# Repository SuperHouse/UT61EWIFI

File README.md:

UNI-T UT61E Multimeter WiFi Interface
=====================================

The UNI-T UT61E multimeter has an opto-isolated output port that
streams data, including the currently selected range and reading.

This project is a WiFi adapter that attaches to the output port
and reports the data via WiFi or USB.

The example firmware reads the data packet from the multimeter and
publishes it to an MQTT broker, and also outputs it via the USB
port at 115200bps.

NOTE: The Rx data pin has been changed from D0 (GPIO16) in the
v1.0 design to D5 (GPIO14) in v1.1. Photos show a v1.0 PCB that
has been patched to the new Rx data pin.

More details:

  http://www.superhouse.tv/ut61ewifi

Releases
--------
See latest release here: (https://github.com/SuperHouse/UT61EWIFI/releases)[https://github.com/SuperHouse/UT61EWIFI/releases]  

Clients
--------
To build the app locally, you can run ```bash ./Clients/build/build.sh``` from the ```/``` (root) of this repo.  
It will run a build of all the clients. (*nodeJS v16 and bash are required*)

Hardware
--------
The "Hardware" directory contains the PCB design as an EAGLE project.
EAGLE PCB design software is available from Autodesk free for
non-commercial use.

Firmware
--------
The "Firmware" directory contains example firmware as an Arduino
project.

The Wemos D1 Mini used in the adapter has an Espressif ESP8266 MCU. 
This is not supported by default by the Arduino IDE, so the first 
step is to install a board profile to suit.

Full steps are explained here:

<https://randomnerdtutorials.com/how-to-install-esp8266-board-arduino-ide/>

Then select: 

  Tools -> Board -> ESP8266 Boards -> "WEMOS(LOLIN) D1 Mini (clone)".

Other ESP8266 board profiles may also work, depending on the specific 
D1 mini that you use.

Two libraries are also required. Install using the Arduino library manager: 

 * "PubSubClient" by Nick O'Leary
 * "NeoPixel" by Adafruit

Credits
-------
  * Jonathan Oxer <jon@oxer.com.au>
  * CableTie <https://github.com/cabletie>
  * Aaron Knox <aaron@makerdock.io>
  * Mitchell Robert <https://github.com/mrinc>

License
-------
Copyright 2021 SuperHouse Automation Pty Ltd  www.superhouse.tv  

The hardware portion of this project is licensed under the TAPR Open
Hardware License (www.tapr.org/OHL). The "license" folder within this
repository contains a copy of this license in plain text format.

The software portion of this project is licensed under the Simplified
BSD License. The "licence" folder within this project contains a
copy of this license in plain text format.

The UNI-T logo is the trademark of Uni-Trend Technology (China) Co., Ltd.

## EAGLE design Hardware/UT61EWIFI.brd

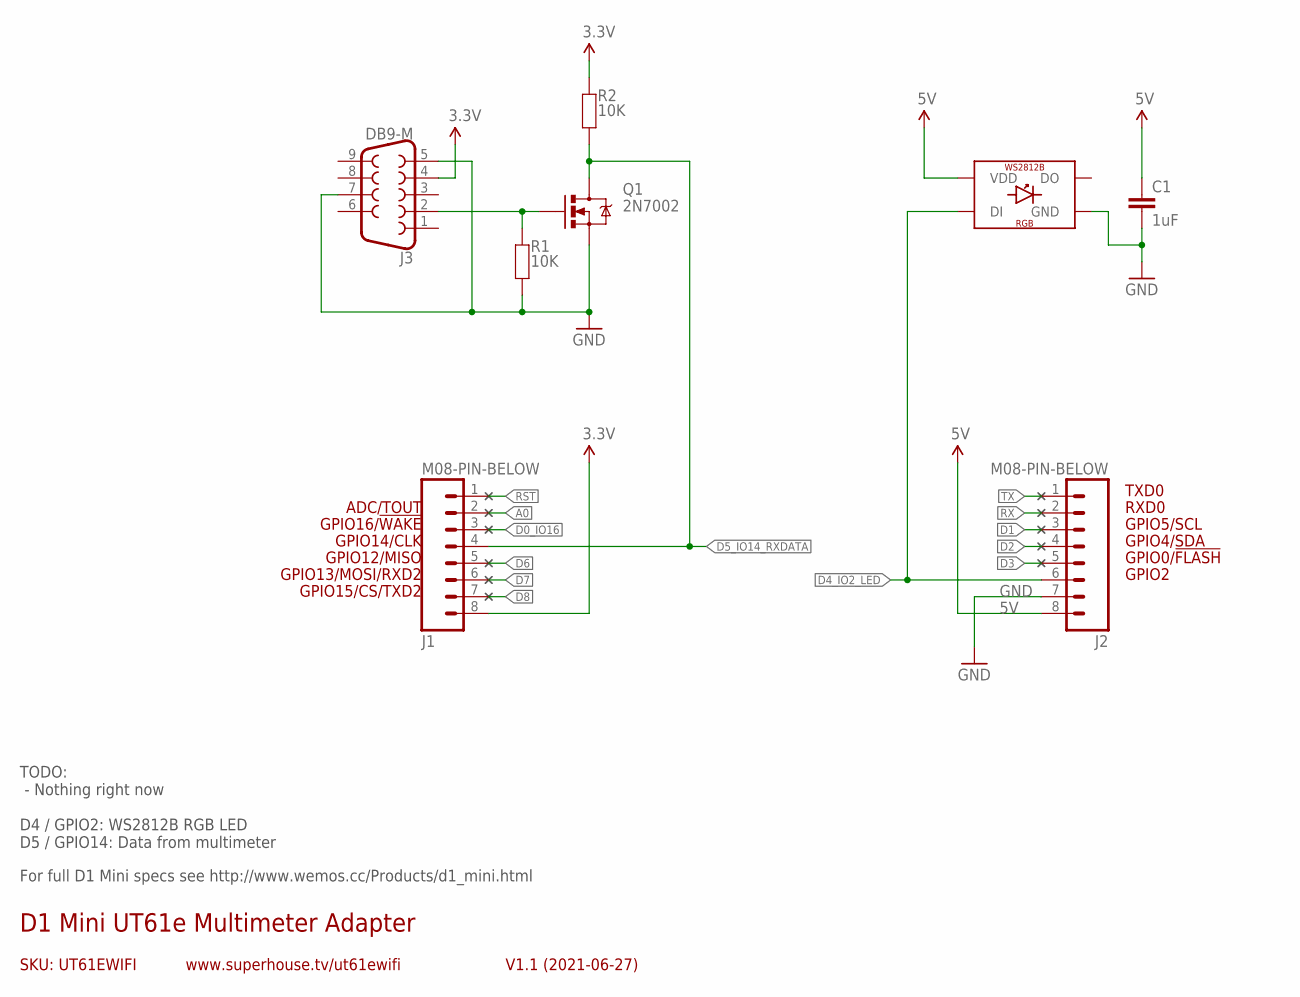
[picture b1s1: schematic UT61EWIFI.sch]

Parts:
C1: 1uF; C0603
J1, J2: M08-PIN-BELOW; 1X08-P-BELOW
J3: DB9-M; DB9-PCB-PLUG
LED1: WS2812B
Q1: 2N7002; SOT23-3
R1, R2: 10K; R0603

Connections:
3.3V: J1.8, J3.4, R2.2
5V: C1.1, J2.8, LED1.1-VDD (VDD)
A0: J1.2
D0_IO16: J1.3
D1: J2.3
D2: J2.4
D3: J2.5
D4_IO2_LED: J2.6, LED1.4-DIN (DI)
D5_IO14_RXDATA: J1.4, Q1.3 (D), R2.1
D6: J1.5
D7: J1.6
D8: J1.7
GND: C1.2, J2.7, J3.5, J3.7, LED1.3-GND (GND), Q1.2 (S), R1.1
unnamed: J3.2, Q1.1 (G), R1.2
RST: J1.1
RX: J2.2
TX: J2.1

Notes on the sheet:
GPIO2
GPIO0/!FLASH
GPIO12/MISO
GPIO4/SDA
GPIO5/SCL
RXD0
TXD0
GPIO13/MOSI/RXD2
GPIO14/CLK
GPIO15/CS/TXD2
GPIO16/!WAKE
SKU: UT61EWIFI
D1 Mini UT61e Multimeter Adapter
V1.1 (2021-06-27)
www.superhouse.tv/ut61ewifi
ADC/TOUT
TODO: - Nothing right now D4 / GPIO2: WS2812B RGB LED D5 / GPIO14: Data from multimeter
For full D1 Mini specs see http://www.wemos.cc/Products/d1_mini.html

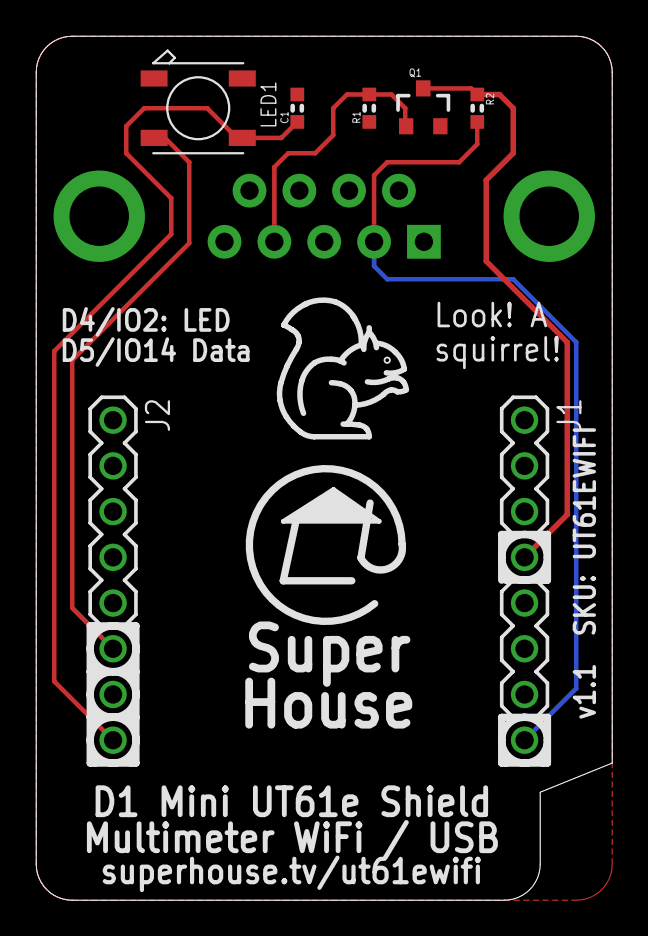
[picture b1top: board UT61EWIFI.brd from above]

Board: 2 copper layers, 32.0 x 48.0 mm, 8 parts (1 on the bottom side), 6 nets.

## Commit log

2021-04-03 Created repo
2021-04-03 Added files copied from AXAWIFI project.
2021-04-03 Added voltage regulator. Added IR input.
2021-05-02 Add work-in-progress firmware.
2021-05-02 Added resources directory and schematic.
2021-06-27 Changed multimeter data pin from D0 to D5 for v1.1 release.
2021-06-27 Added version of firmware for D1 Mini.
2021-06-27 Renamed ESP32 version of firmware for clarity.
2021-06-27 Added info about mistake in UT61E schematic and comparitors.
2021-06-28 Added images.
2021-06-28 Added image into README.
2021-06-28 Scaled down image.
2021-06-29 Resized preview image.
2021-06-29 Added photos of real board.
2021-06-29 Replaced render with photo of the real board.
2021-06-30 Added support for WS2812B status LED.
2021-07-05 Improved boot status display on RGB LED. Removed legacy ESP32 code. Changed device ID to upper case in MQTT topics and MQTT client id. Display link to project page in terminal at startup.
2021-07-12 Restructured schematic to make it neater.
2021-07-23 Added Aaron Knox's Node-RED client.
2021-07-23 Formatting fix.
2021-07-23 Added beginning of protocol definition.
2021-07-24 Start work towards changing from PubSubClient to ArduinoMqttClient
2021-07-25 Updated Node Red Client for better support with Home Assistant Node Red Add-on installations. Updated Node Red client to use the latest JSON Schema. Updated Node Red Client README.md to reflect chang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
2021-07-26 Add decoding (basic) and publish JSON via MQTT
2021-07-27 Add ut61e_measure library to decode raw messages.
2021-07-27 Added use of ut61e_measure library
2021-07-27 Tidy up #includes
2021-07-27 Add note about c++ exceptions
2021-07-27 More comments
2021-07-27 Corrected attribution
2021-08-09 Initial "Display" version
2021-08-09 Rename .ino to project name
2021-08-09 Updated Node Red client to support new JSON schema for initial firmware created by CableTie
2021-08-09 Added contributors and license files.
2021-08-10 Cleaned up formatting Removed extended parameter from parse() Strip leading zeroes from displaystring Removed extra JSON + JSON_X (now just JSON. Added 'OL' and 'UL' to dislay_string at appropriate t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
2021-08-11 Change to full display decode.
2021-08-11 Added README.md
2021-08-12 Updated UI to support latest developments on the UT61EWiFiD1Mini firmware. Added support for Range, Hold and the following modes continuity, diode. Also added in new Icon for Low Battery status indic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
2021-08-12 Full update of ut61e_display REAME.md Fix detection of PMAX and PMIN
2021-08-12 Added display_digits generation Fixed display_string generation Added proper treatment of hold flag
2021-08-15 Adding full stack VueJS UI for structured development. Created a dummy server to simulate data
2021-08-15 Added graphing to webUI. cleanups and added more log data to work with
2021-08-15 Added theming
2021-08-18 Finished themes
2021-08-18 Starting github ci
2021-08-18 Updating ci build for a single node version, and chaining cmds
2021-08-18 Automating build for node-red ui. Cleanups and build updates.
2021-08-18 Node-red specific release
2021-08-18 Fixing case for RED from Red
2021-08-18 Build updates for path
2021-08-18 Single release, multiple files
2021-08-18 Updating readme to include that the user must cd into the project dir and have vue-cli installed. audit update
2021-08-18 Package updates for build bugs
2021-08-18 Readme fix
2021-08-19 Adding easier bypass url method
2021-08-19 Build fixes with replace causing issues, nodejs touchups
2021-08-19 fixing some path issues and js build issues
2021-08-19 Fixing WS issues, cleanup. Storing found server in cookie for quicker access later. delay after finding ws server. more info on LCD
2021-08-28 bugfixes and UI changes for aaron
2021-08-28 Adding routing engine and tools
2021-08-28 add pak for desktop
2021-08-28 licenses and authors
2021-08-28 Major build improvements and desktop app with build
2021-08-28 Added release versioning.
2021-08-28 release versioning updates
2021-08-28 version month fixes. output var fixes
2021-08-28 missed one 's'
2021-08-29 Speed improvements on initial connection. Touchups on server definitions for easier use. More logging for loading
2022-02-28 fixing vue.js issues
2022-02-28 Added page selector
2022-02-28 NPM Update. Added pages file. Changed default nodered-web-ui content to relay release download link
2022-02-28 Using local storage instead of cookies ... since they are going away
2022-02-28 Removed cookies package. Added a safety net for weird firefox behaviour during dev
2022-02-28 Updated versions. Initial dev-build system.
2022-02-28 Updated build proc
2022-02-28 Removing standard build for now from dev build
2022-02-28 Refactored the UI
2022-03-03 Adding credits ref
2022-03-03 Adding ability for dummy server to relay TO MQTT as well for testing
2022-03-03 Added missing async...
2022-03-03 Build changes in prep for multi-plat-build. Dev build can build desktop app
2022-03-27 Merged feature/CIDevelopmentForMultiPlatformBuilds
2022-03-27 author change
2022-03-27 added releases URL to readme
2026-03-13 Added info about required board profile and libraries.

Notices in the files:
Hardware/UT61EWIFI.brd:
(C)2021 SuperHouse
Open Hardware License
parts and their libraries:
freetronics-original: Licensing: CC v3.0 Share-Alike You are welcome to use this library for commercial purposes.
